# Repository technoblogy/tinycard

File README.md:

# TinyCard
A simple text game maker to allow children to create short adventure games, interactive stories, surveys, or quizzes.

For more information see <http://www.technoblogy.com/show?51KR>.

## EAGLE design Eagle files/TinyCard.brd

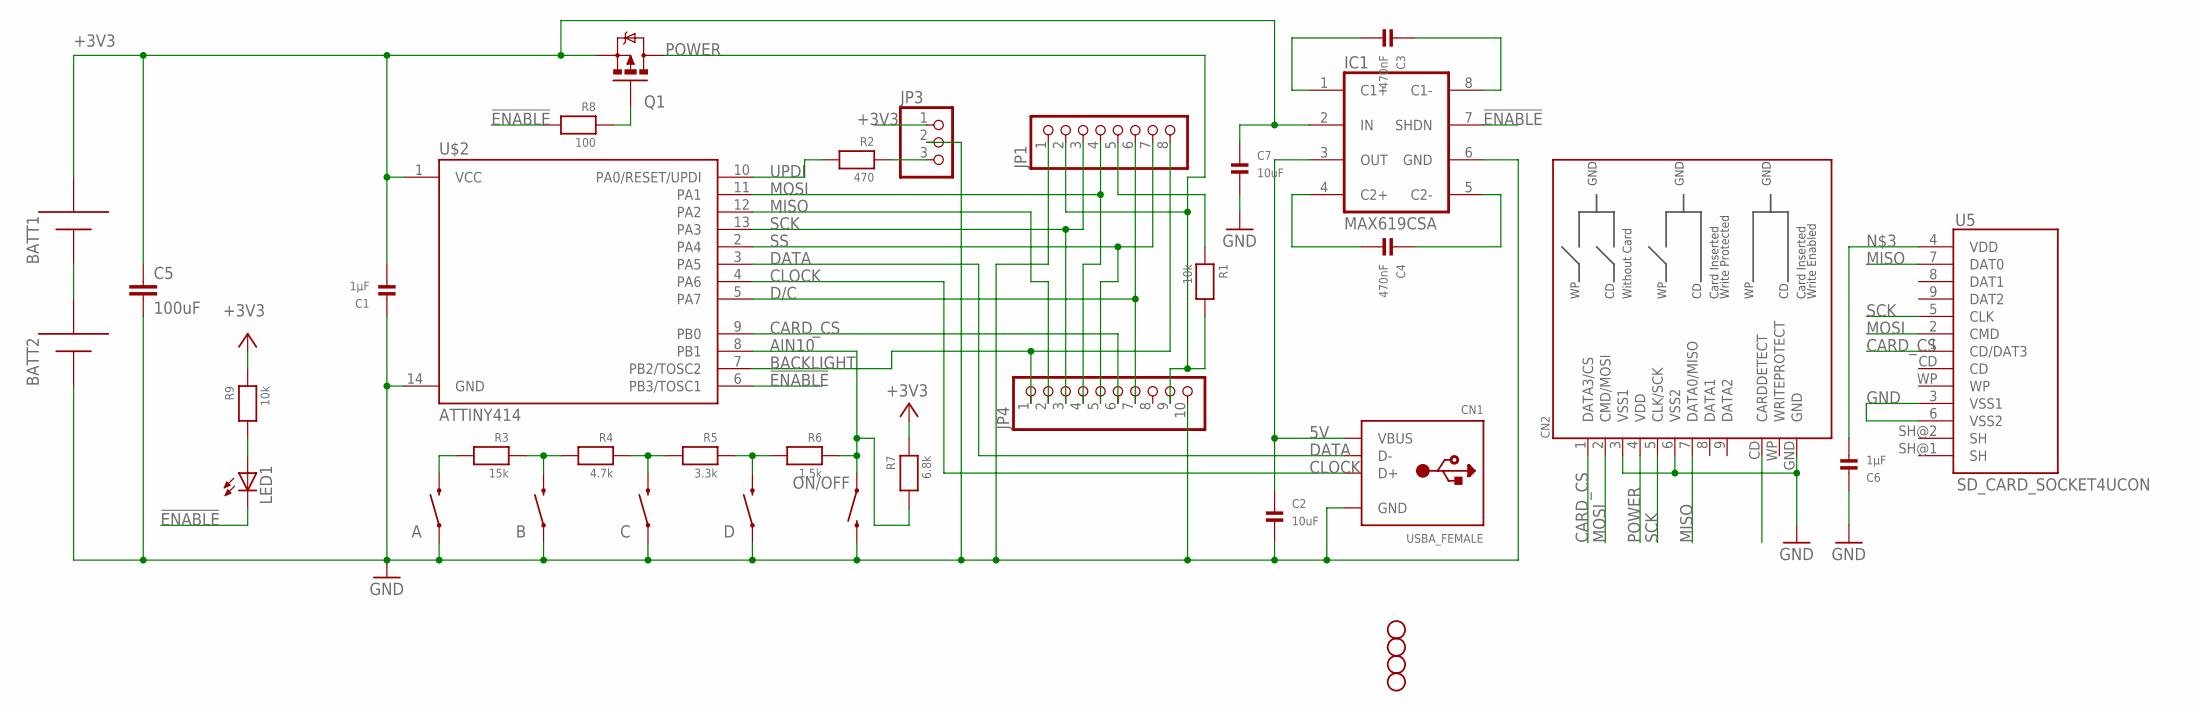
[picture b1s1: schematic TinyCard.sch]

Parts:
A: SWITCH-MOMENTARY-212MM; TACTILE-PTH-12MM
B: SWITCH-MOMENTARY-212MM; TACTILE-PTH-12MM
BATT1, BATT2: AAA; 12BH412
C: SWITCH-MOMENTARY-212MM; TACTILE-PTH-12MM
C1, C6: 1µF; _0805MP
C2, C7: 10uF; _0805MP
C3, C4: 470nF; _0805MP
C5: 100uF; 1210
CN1: USBA_FEMALE; USB_HOST-PTH
CN2: SDCARD; SDCARD_SMT_4U06132
D: SWITCH-MOMENTARY-212MM; TACTILE-PTH-12MM
IC1: MAX619CSA; SO08
JP1: HEADER-1X8ROUND; 1X08_ROUND
JP3: HEADER-1X3ROUND; 1X03_ROUND
JP4: HEADER-1X10ROUND; 1X10_ROUND
JP5, JP6, JP7, JP8: STAND-OFF
LED1: LEDCHIPLED_0805; CHIPLED_0805
ON/OFF: SWITCH-MOMENTARY-2PTH; TACTILE-PTH
Q1: MOSFET-PCHANNELSMD; SOT23-3
R1, R9: 10k; _0805MP
R2: 470; _0805MP
R3: 15k; _0805MP
R4: 4.7k; _0805MP
R5: 3.3k; _0805MP
R6: 1.5k; _0805MP
R7: 6.8k; _0805MP
R8: 100; _0805MP
U5: SD_CARD_SOCKET4UCON; SDCARD_4UCONN
U$2: ATTINY414; SO14

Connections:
5V: C2.1, CN1.VBUS, IC1.3 (OUT)
!ENABLE: IC1.7 (SHDN), LED1.C, R8.2, U$2.6 (PB3/TOSC1)
+3V3: BATT1.+, C1.2, C5.1, C7.1, IC1.2 (IN), JP3.1, Q1.2 (S), R7.1, R9.1, U$2.1 (VCC)
AIN10: ON/OFF.1, R6.1, R7.2, U$2.8 (PB1)
BACKLIGHT: JP1.8, JP4.1, U$2.7 (PB2/TOSC2)
CARD_CS: CN2.1 (DATA3/CS), JP4.6, U5.1 (CD/DAT3), U$2.9 (PB0)
CLOCK: CN1.D+, U$2.4 (PA6)
D/C: JP1.6, JP4.7, U$2.5 (PA7)
DATA: CN1.D-, U$2.3 (PA5)
GND: A.1, B.1, BATT2.-, C.1, C1.1, C2.2, C5.2, C6.1, C7.2, CN1.GND, CN2.3 (VSS1), CN2.6 (VSS2), CN2.GND, D.1, IC1.6 (GND), JP1.1, JP3.2, JP4.10, ON/OFF.3 (2), U5.3 (VSS1), U5.6 (VSS2), U$2.14 (GND)
MISO: CN2.7 (DATA0/MISO), JP4.2, U5.7 (DAT0), U$2.12 (PA2)
MOSI: CN2.2 (CMD/MOSI), JP1.4, JP4.4, U5.2 (CMD), U$2.11 (PA1)
unnamed: BATT1.-, BATT2.+
unnamed: A.3 (2), R3.2
unnamed: C6.2, U5.4 (VDD)
unnamed: JP1.5, R1.1
unnamed: C3.2, IC1.1 (C1+)
unnamed: C3.1, IC1.8 (C1-)
unnamed: B.3 (2), R3.1, R4.2
unnamed: C.3 (2), R4.1, R5.2
unnamed: D.3 (2), R5.1, R6.2
unnamed: LED1.A, R9.2
unnamed: C4.2, IC1.4 (C2+)
unnamed: C4.1, IC1.5 (C2-)
unnamed: Q1.1 (G), R8.1
unnamed: JP3.3, R2.1
POWER: CN2.4 (VDD), JP1.2, JP4.9, Q1.3 (D), R1.2
SCK: CN2.5 (CLK/SCK), JP1.3, JP4.3, U5.5 (CLK), U$2.13 (PA3)
SS: JP1.7, JP4.5, U$2.2 (PA4)
UPDI: R2.2, U$2.10 (PA0/RESET/UPDI)

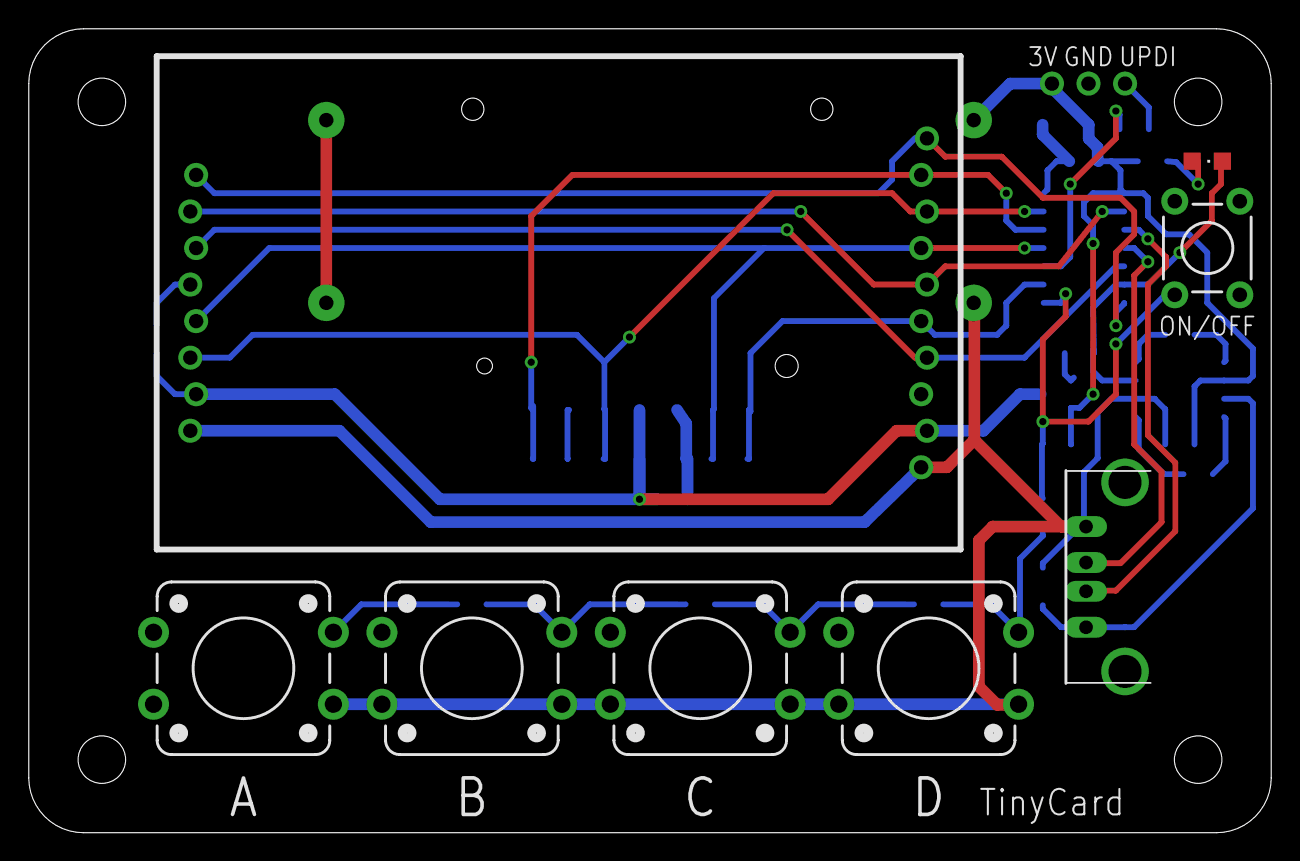
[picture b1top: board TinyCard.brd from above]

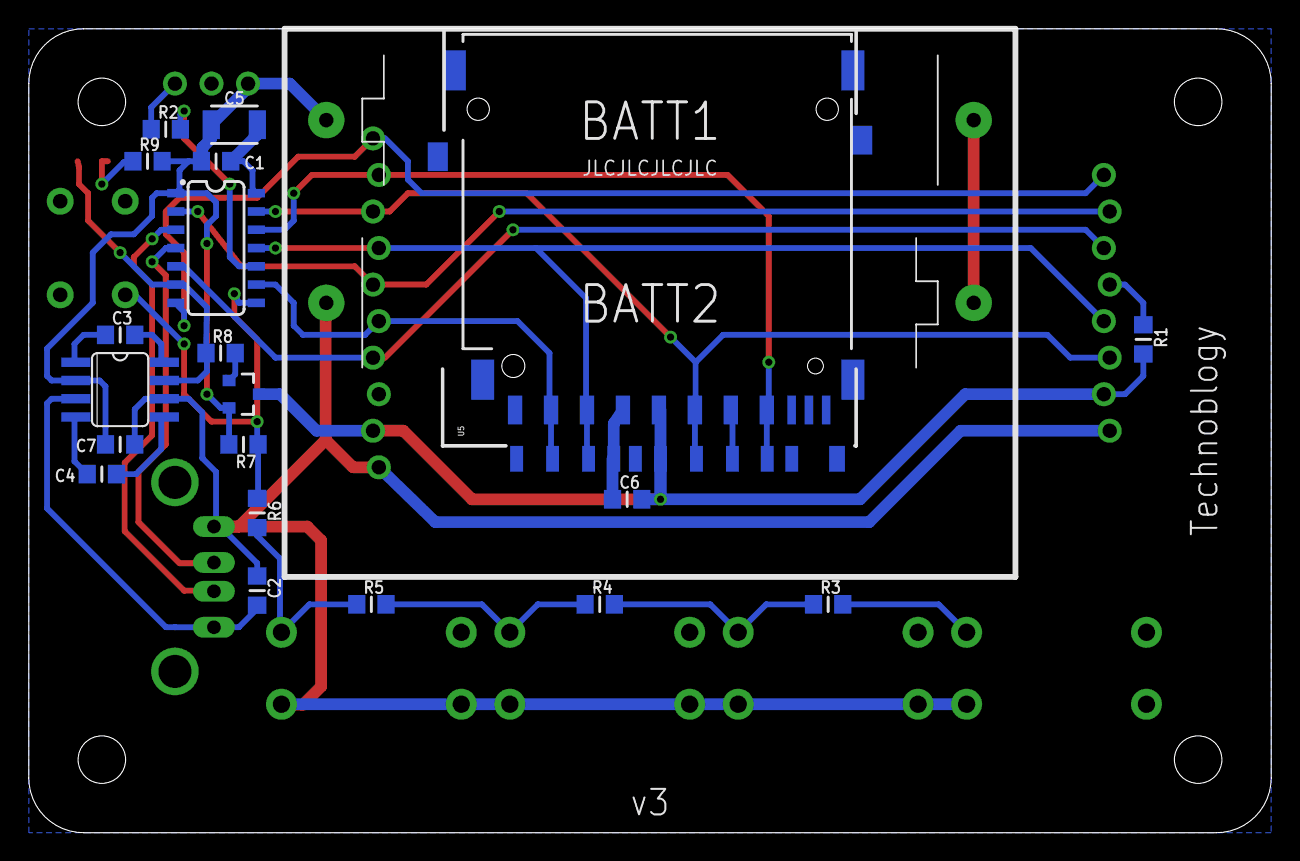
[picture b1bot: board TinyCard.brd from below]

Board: 2 copper layers, 86.4 x 55.9 mm, 37 parts (23 on the bottom side), 30 nets.

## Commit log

2025-03-25 Version 1 - 25th March 2025
2025-03-27 Version 2 - 27th March 2025
    Decoupling capacitors
2025-03-30 Temporarily removed
2025-04-08 Version 3 - 8th April 2025

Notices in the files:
parts and their libraries:
microbuilder: This work is placed in the public domain, and may be freely used for commercial and non-commercial work with the following conditions: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
technoblogy: Licensing: Creative Commons ShareAlike 4.0 International - https://creativecommons.org/licenses/by-sa/4.0
